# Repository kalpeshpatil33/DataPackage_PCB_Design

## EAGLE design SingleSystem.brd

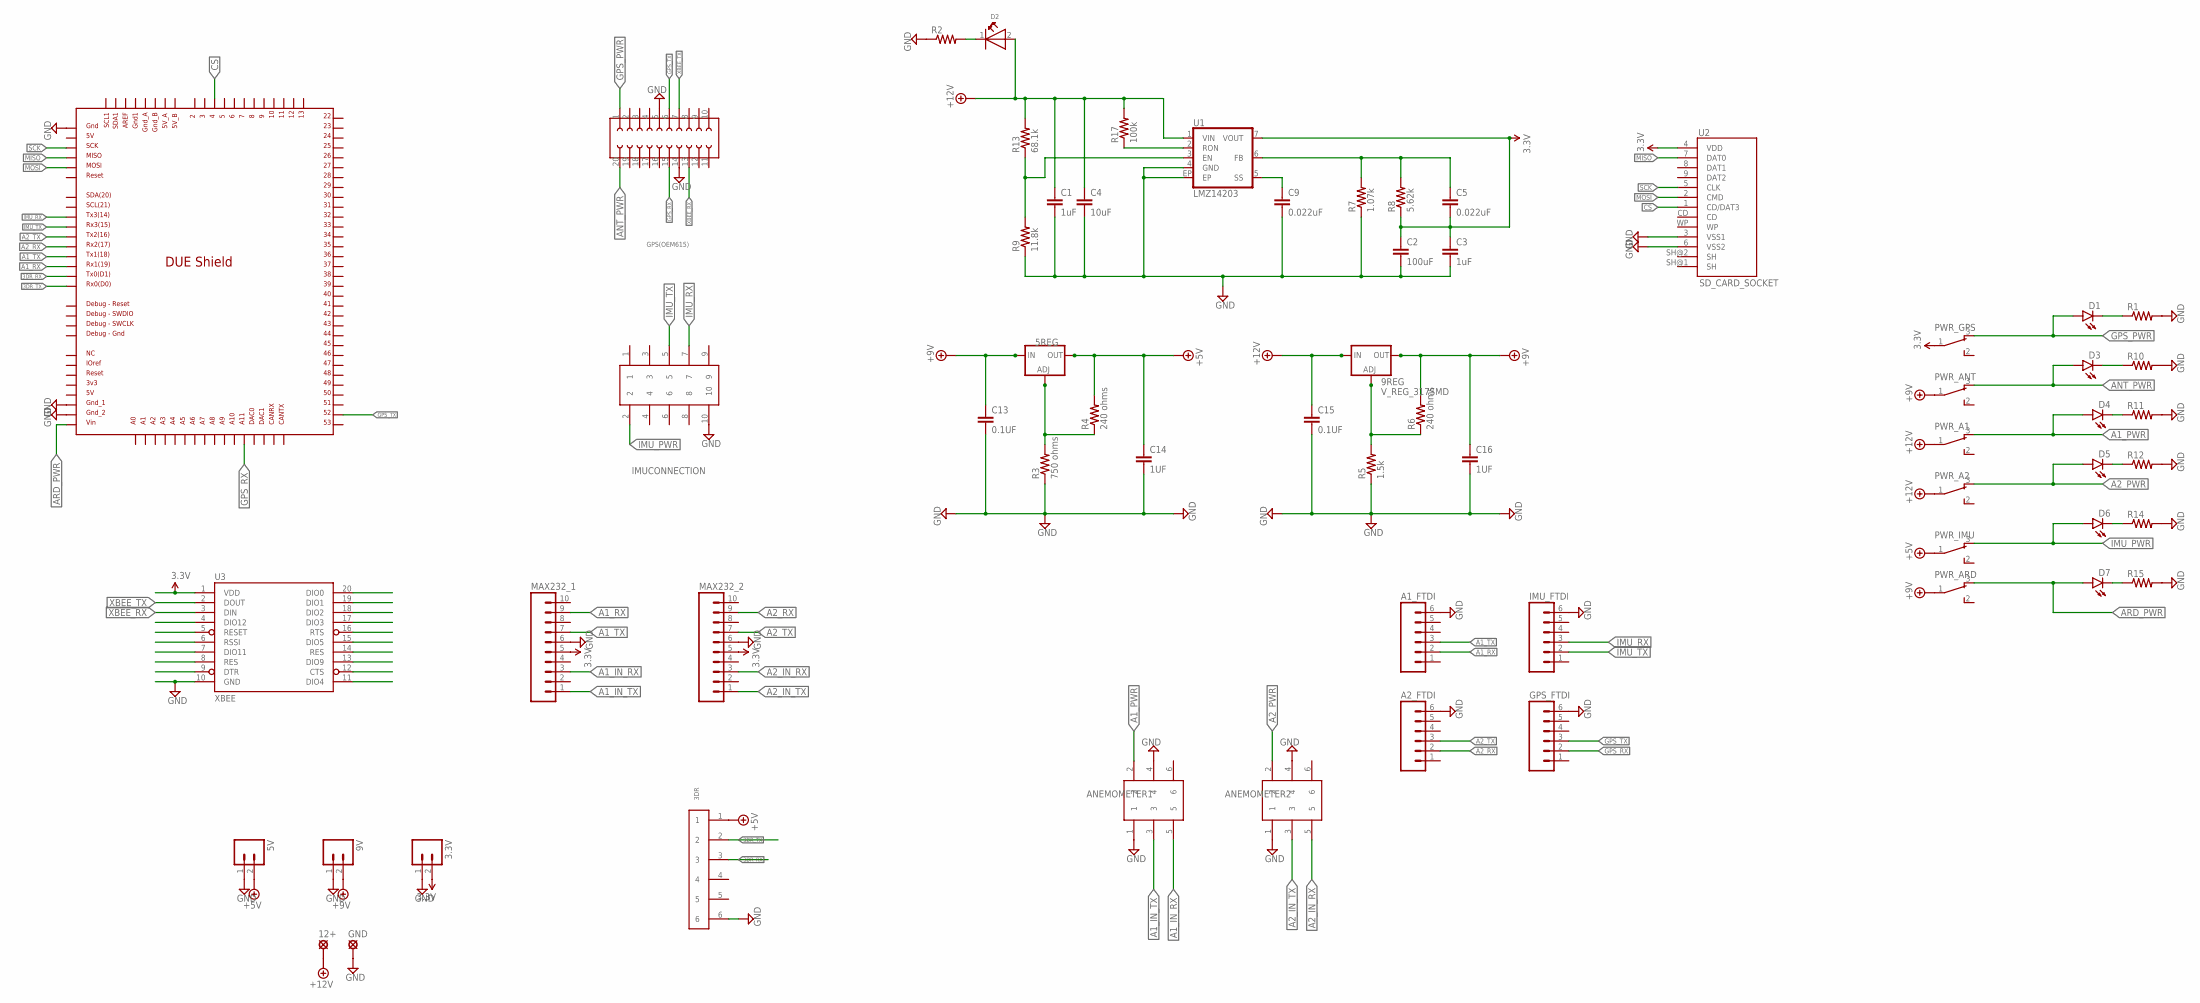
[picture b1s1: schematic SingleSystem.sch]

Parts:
3.3V, 5V, 9V: M02; 02P
3DR: 653006114822
5REG, 9REG: V_REG_317SMD; SOT223
12+: SE14
A1_FTDI, A2_FTDI: M06; 06P
ANEMOMETER1, ANEMOMETER2: 61200622323
C1, C3: 1uF; 0805; MPN 1C10Z5U104M050R
C2: 100uF; 1206
C4: 10uF; 0805
C5, C9: 0.022uF; 0603-CAP
C13, C15: 0.1UF; 0805
C14, C16: 1UF; 0805
D1, D3, D4, D5, D6, D7: LED-FKIT-1206; FKIT-LED-1206
D2: WL-SMCW-150120BS75000-B; 1206
GND: SE14
GPS(OEM615): 62002021821
GPS_FTDI: M06; 06P
IMUCONNECTION: 62501021621
IMU_FTDI: M06; 06P
MAX232_1, MAX232_2: M10; 10P
PWR_A1, PWR_A2: 450301014042
PWR_ANT: 450301014042
PWR_ARD: 450301014042
PWR_GPS: 450301014042
PWR_IMU: 450301014042
R1, R2, R10, R11, R12, R14, R15: R-US_M2012; M2012
R3: 750 ohms; M2012
R4, R6: 240 ohms; M2012
R5: 1.5k; M2012
R7: 1.07k; M2012
R8: 5.62k; M2012
R9: 11.8k; M2012
R13: 68.1k; M2012
R17: 100k; M2012
U1: LMZ14203; TO-PMOD-7
U2: SD_CARD_SOCKET; SD_1:1
U3: XBEE; XBEE-1
U$1: DUE(NORMAL)

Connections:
3.3V: 3.3V.2, C2.1, C3.1, C5.2, MAX232_1.5, MAX232_2.5, PWR_GPS.1, R8.1, U1.7 (VOUT), U2.4 (VDD), U3.1 (VDD)
3DR_RX: 3DR.3, U$1.TX0
3DR_TX: 3DR.2, U$1.RX0
+5V: 3DR.1, 5REG.2 (OUT), 5V.2, C14.1, PWR_IMU.1, R4.2
+9V: 5REG.3 (IN), 9REG.2 (OUT), 9V.2, C13.1, C16.1, PWR_ANT.1, PWR_ARD.1, R6.2
+12V: 9REG.3 (IN), 12+.MP, C1.1, C4.1, C15.1, D2.2 (A), PWR_A1.1, PWR_A2.1, R13.2, R17.2, U1.1 (VIN)
A1_IN_RX: ANEMOMETER1.5, MAX232_1.3
A1_IN_TX: ANEMOMETER1.3, MAX232_1.1
A1_PWR: ANEMOMETER1.2, D4.A, PWR_A1.3
A1_RX: A1_FTDI.2, MAX232_1.9, U$1.RX1
A1_TX: A1_FTDI.3, MAX232_1.7, U$1.TX1
A2_IN_RX: ANEMOMETER2.5, MAX232_2.3
A2_IN_TX: ANEMOMETER2.3, MAX232_2.1
A2_PWR: ANEMOMETER2.2, D5.A, PWR_A2.3
A2_RX: A2_FTDI.2, MAX232_2.9, U$1.RX2
A2_TX: A2_FTDI.3, MAX232_2.7, U$1.TX2
ANT_PWR: D3.A, GPS(OEM615).20, PWR_ANT.3
ARD_PWR: D7.A, PWR_ARD.3, U$1.VIN
CS: U2.1 (CD/DAT3), U$1.4
GND: 3.3V.1, 3DR.6, 5V.1, 9V.1, A1_FTDI.6, A2_FTDI.6, ANEMOMETER1.1, ANEMOMETER1.4, ANEMOMETER2.1, ANEMOMETER2.4, C1.2, C2.2, C3.2, C4.2, C9.2, C13.2, C14.2, C15.2, C16.2, GND.MP, GPS(OEM615).5, GPS(OEM615).14, GPS_FTDI.6, IMUCONNECTION.10, IMU_FTDI.6, MAX232_1.6, MAX232_2.6, R1.2, R2.1, R3.1, R5.1, R7.1, R9.1, R10.2, R11.2, R12.2, R14.2, R15.2, U1.4 (GND), U1.EP, U2.3 (VSS1), U2.6 (VSS2), U3.10 (GND), U$1.5V_ICSP, U$1.GND_1, U$1.GND_2
GPS_PWR: D1.A, GPS(OEM615).1, PWR_GPS.3
GPS_RX: GPS(OEM615).15, GPS_FTDI.2, U$1.A11
GPS_TX: GPS(OEM615).6, GPS_FTDI.3, U$1.52
IMU_PWR: D6.A, IMUCONNECTION.2, PWR_IMU.3
IMU_RX: IMUCONNECTION.7, IMU_FTDI.3, U$1.TX3
IMU_TX: IMUCONNECTION.5, IMU_FTDI.2, U$1.RX3
MISO: U2.7 (DAT0), U$1.MISO_ICSP
MOSI: U2.2 (CMD), U$1.MOSI_ICSP
unnamed: 5REG.1 (ADJ), R3.2, R4.1
unnamed: 9REG.1 (ADJ), R5.2, R6.1
unnamed: R9.2, R13.1, U1.3 (EN)
unnamed: R17.1, U1.2 (RON)
unnamed: C9.1, U1.5 (SS)
unnamed: D2.1 (K), R2.2
unnamed: C5.1, R7.2, R8.2, U1.6 (FB)
unnamed: D1.C, R1.1
unnamed: D3.C, R10.1
unnamed: D4.C, R11.1
unnamed: D5.C, R12.1
unnamed: D6.C, R14.1
unnamed: D7.C, R15.1
SCK: U2.5 (CLK), U$1.SCK_ICSP
XBEE_RX: GPS(OEM615).13, U3.3 (DIN)
XBEE_TX: GPS(OEM615).7, U3.2 (DOUT)

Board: 2 copper layers, 61 parts (29 on the bottom side), 44 nets, no tracks yet.

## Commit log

2016-10-14 Inital PCB file pulled from Google Drive

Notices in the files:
parts and their libraries:
Wire_to_Board_Connectors_rev15d: Copyright: Würth Elektronik
SparkFun-PowerIC: Licensing: Creative Commons ShareAlike 4.0 International - https://creativecommons.org/licenses/by-sa/4.0
